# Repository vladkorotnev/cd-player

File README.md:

# ESPer CDP: DIY CD Player with Extra Features

## Index

* [Why a CD Player?](#why-a-cd-player)
* [The structure of an ESPer System](#the-structure-of-an-ESPer-system)
* [Contributing to ESPer](#contributing-to-esper)
* [Using ESPer in your own designs](#using-esper-in-your-own-designs)
* [Where to go further](#where-to-go-further)

## Why a CD Player?

Indeed, it is a very odd project to start in 2025, and continue in 2026. For most people listening to music is a click of a button away in a streaming service, or a local player.

I will not go into the argument of owning vs. borrowing and, frankly, I keep to a more tame stance on the question: it's fine not to own every single piece of media you consume. It's *bad* to *not have an option* to own it, but you also probably don't want to hoard every single that you're only gonna play once and forget about it the day after.

For me the reasons to create ESPer ultimately boil down to:

* **Personal Preference:** I have been collecting CDs for my entire life, with a [very sizeable number](https://www.discogs.com/user/vladkorotnev/collection) to date. My dad has been doing that as well for a good 2/3rds of his life. The CD format is tactile enough to be more interesting than a mouse click, yet convenient enough to be turned into one when the need arises, in contrast to e.g. vinyl. So a CD player to me is as essential as a fridge or a TV, for example. And sure, there are people who don't want one, or don't want a TV, and that's their choice to make.
* **Personal Preference 2:** For a while, microcontrollers in general have not been a very accessible platform. After the Arduino came out some people went as far as to make [CD-players on those](http://singlevalve.web.fc2.com/Atapiduino/atapiduino.htm), but to a newbie me back in the day the circuits looked intimidating. These days manufacturing even custom PCBs is very cheap and options to design them are ample, so it's a chance to take a spin on what I've wanted to do for years.
* **Sustainability:** While CDs are still somewhat active, the *good* players are much less so. You have the usual big brands in massive champagne colored cases which look great and work great, but priced somewhat ridiculous. If you're lucky, you can go to a second-hand store and grab an older model for a more modest price — but who knows if its' days are counted. And you have a lot of the cheaper, bottom of the barrel stuff — i.e. those modern-day players that somehow go out of their way to mess up gapless playback ("tracks" on a CD are akin to a table of contents in a book — it's a list of places where they start and end, alongside a single uninterrupted chunk of audio). Having an open platform based around a commodity item — the computer CD drive — means that as long as one of those is around and working, the player will work, too. Usually when they fail they actually need just a new belt for the tray — and if it's something more fatal then you can always just find a new one.
* **Preservation:** Some old CD drives were *nuts*. Slot loaders? Pioneer made a few, Apple had Matsushita build them for decades. 3.5-inch desktop units? Hey, I can fit [four discs in that](https://youtu.be/9ajyFVKGGHI), says Nakamichi/NEC. Hold my beer, [I'll do SIX!](https://www.instagram.com/p/DFPdWDMTqwi/), responds TEAC. And then those things become basically trash, because no modern computer can really utilize it (and let's be honest, if it can, it probably already has a way more capable drive installed in terms of supported formats). So why not have one sit on your desk and play music instead of decaying in the closet?

## The Structure of an ESPer System

The very first edition (codenamed `ESPER_OG_8M` in the firmware) used a singular, somewhat hastily routed PCB with I2C expanders for the IDE bus. This had its' flaws and strengths, but it's mostly legacy now.

The new ESPer platform going forward consists of four main parts:

1. Processor board: this is where the ESP32 lives along with the buttons and LEDs. Not sure if it's a good idea to combine the buttons onto it but for the compact build it makes more sense.
2. Drive board: this is what plugs into the drive. The flavor depends on the drive you have. The currently planned versions are:
   1. SATA Slimline: you can use this with a laptop SATA drive, because no readymade adapters exist on the market.
   2. IDE/ATAPI/PATA: comes fitted with a plug that can plug right into the drive, a pin header to use a ribbon cable, or both to allow for dual drives in a more compact way than a longer cable. A JAE KX14 50-pin connector can be fitted to use an older laptop IDE drive, or you can connect this to an off-the-shelf IDE-to-SATA translation board to use a desktop-sized SATA drive.
3. IO board: this is what provides power to the whole shebang, and also contains the DAC for the sound to come out of.
   1. Compact variant: made to fit around a laptop drive, has a USB-C 5V input, a DAC, line out 3.5mm jack, headphone jack and a headphone volume wheel.
   2. (Planned) HiFi variant: made with less thoughts given to size for use primarily with desktop drives. Triggers USB-C at 15V or takes a 12V barrel jack, and delivers a separate power line to the bigger desktop drive, while housing a DAC with an RCA line-out, an SPDIF out and a TOSLINK out. Perhaps someday also SPDIF input?
4. Display board: this houses just the display and the infrared receiver alongside it.

The infrared remote is a knockoff Sony RM-D335 with a replaced label to match the functions of the remote in the ESPer menus.

### Accessory Port

The Processor Board is equipped with an "Accessory Port". The use of that is specific to a build, but essentially it's a MOSFET-switched 5V output good for up to an amp.

The logic of it is set by the straps on the main board:

* `000`: the accessory port is active when the player is turned on, and in a non-menu state. This is a good mode to hook up a pass through relay so that another sound source can be chained on the same line for when the player is turned off.
* (planned) `001`: enables the Zoetrope mode. An LED tape installed into a window on the CD drive shall be connected to the output in this mode. When the CD mode is active and a disc is present, the LEDs pulse at a frequency roughly on par with the disc's rotation, chosen experimentally. This allows, at the right lighting conditions, to keep the CD label readable even though it spins very fast. When there is no disc, the LEDs are constantly lit at half the brightness. When a non-CD mode is active, the LEDs turn off.
* Others: reserved.

## Contributing to ESPer

While I do have somewhat strong feelings about that thing being pushed on everyone from all sides for the past few years, I also do acknowledge that in the right hands it does accelerate by a good amount without significant quality reduction. However, to achieve that, we must keep ourselves using the tool to a very high standard.

* **Please test your code.** Not as in unit-tests, but as in flash the firmware and daily drive it for a few. If you have the OG and the Neo revisions, that's awesome! If not, test on which one you have. Get a feel for how it operates, if the UX is any good or there are some annoyances in the operation of the device. If there are, please list them out and we can fix them together. **PRs from users who don't own the hardware will not be accepted in principle.**
* **No machine-generated PR body and docs.** For a non-work project like this, it's not about the hustle, but rather the communication. If you did not take care to see and read through what you want to send in and document it properly, this is insulting to everyone involved, as now the other person must dig through your code themselves to see if the text on the label matches what's actually inside the tin.
* **Machine-generated code must still be readable and understandable for a human.** Not all of us use coding agents. Not all of us can even afford them financially, and not all of us are morally comfortable with how things are right now. Comments should be *sufficient* and formatting should be *sane*. A wall of text for every line is probably not it, though [exceptions do happen](https://github.com/vladkorotnev/plasma-clock/blob/main/src/display/akizuki_k875.cpp#L240-L327) (usually the cursed parts). Something that looks like it was run through a JS minifier is definitely not it.
* **Please don't vibe-code in the bad sense of the term.** While most of the above points already cover it, still do think whether you should do something before seeing whether you can push it into the upstream.

## Using ESPer in your own designs

### Using existing PCBs

You are free to use the PCBs officially provided from this repo as files, or from myself as physical products, to build players for your friends and family. You can even do that for sale, although I would appreciate a donation in such case as well, as this has been an enormous amount of work.

In this case, just make sure you flash the right firmware with the right `FVU_FLAVOR` so that online updates work. It's probably best to install the firmware from the online updater so that it already comes with API tokens and such things used by the official upstream.

### Designing new PCBs

If the hardware matches an official board, and an existing FVU flavor can apply, then the same points as above stand.

Otherwise if you want to change e.g. the pin assignments, please fork this repository and create a new HTTP update source. The existing CI scripts should be good enough. You will then need to point the firmware to update from your server instead.

If your variant gains decent following or you plan to produce it en-masse, feel free to open an issue to add it as an officially supported flavor.

## Where to go further

* [Firmware](firm)
* [Schematics](sch)
* [Test CD files and CUE sheet](test-suite)
* [Hoard of ATAPI-related Docs](reference)

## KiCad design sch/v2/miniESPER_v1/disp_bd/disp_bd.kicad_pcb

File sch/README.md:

# ESPer-CDP Project Schematics Archive

## v1: original ESPer design

Folder: [./v1/]

Format: DipTrace (legacy).

Use with the `OG8M` firmware flavor.

Interfaces:

* ATAPI (slow, command-only)
* I2C expansion ("NIXIEOUT", deprecated/unused)
* 8 button inputs, active low
* RS232 to Futaba GP1232 display (160x32 pixels)
* Line out, 12V out

## v1.5: interface prototype

Folder: [./v1_5]

Partial prototype of a fast ATAPI interface using 2x MCP23S17, 74HC4040AP, 74HC32AP and 74HC123AP in DIP package, as well as AE-LLCNV-LVCH16T245 level shifter breakout board.

Use in conjunction with any ESP32 or the v1 board.

No pre-existing board config exists, create one with the following template:

```c
#define BCONF_IDE_TYPE                          IDEBUS_TYPE_CURSED_SPI
#define BCONF_IDE_SPI_NUM                       VSPI
#define BCONF_IDE_SPI_BURST_PIN                 ...
#define BCONF_IDE_SPI_WRITE_PIN                 ...
#define BCONF_IDE_SPI_CS_PIN                    ...
#define BCONF_IDE_SPI_SCK_PIN                   ...
#define BCONF_IDE_SPI_MISO_PIN                  ...
#define BCONF_IDE_SPI_MOSI_PIN                  ...
#define BCONF_IDE_SPI_RST_PIN                   ...
```

# v2

Work in progress

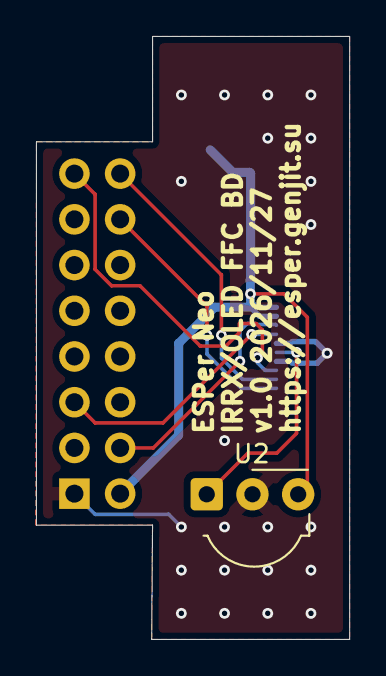
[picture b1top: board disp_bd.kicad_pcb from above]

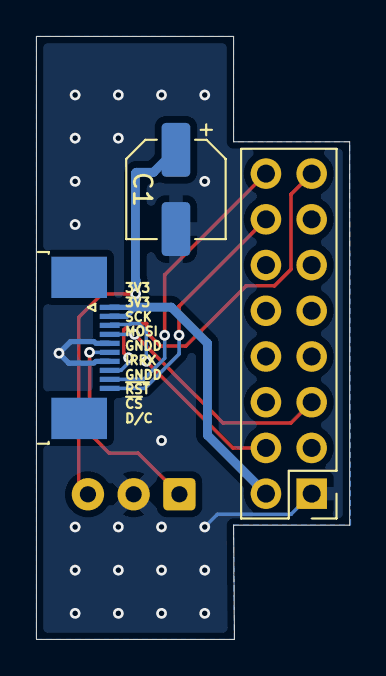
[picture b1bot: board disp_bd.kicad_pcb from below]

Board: 2 copper layers, 17.4 x 33.5 mm, 4 parts (3 on the bottom side), 8 nets.

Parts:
C1: C_Polarized; CP_Elec_5x3
J2: To_Main_Bd; TE_1-1734839-0_1x10-1MP_P0.5mm_Horizontal
OLED1: PinHeader_2x08_P2.54mm_Vertical
U2: TSOP43xx; Vishay_MOLD-3Pin

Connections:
+3V3: C1.1, J2.1, J2.2, OLED1.2 (VCC), U2.3 (Vs)
DISP_CS: J2.9, OLED1.16 (~CS)
DISP_DC: J2.10, OLED1.14 (D/~C)
DISP_MOSI: J2.4, OLED1.5 (MOSI/D1)
DISP_SCK: J2.3, OLED1.4 (SCK/D0)
GNDD: C1.2, J2.5, J2.7, OLED1.1 (GND), U2.2 (GND)
IR_RX: J2.6, U2.1 (OUT)
~RESET: J2.8, OLED1.15 (~RES)

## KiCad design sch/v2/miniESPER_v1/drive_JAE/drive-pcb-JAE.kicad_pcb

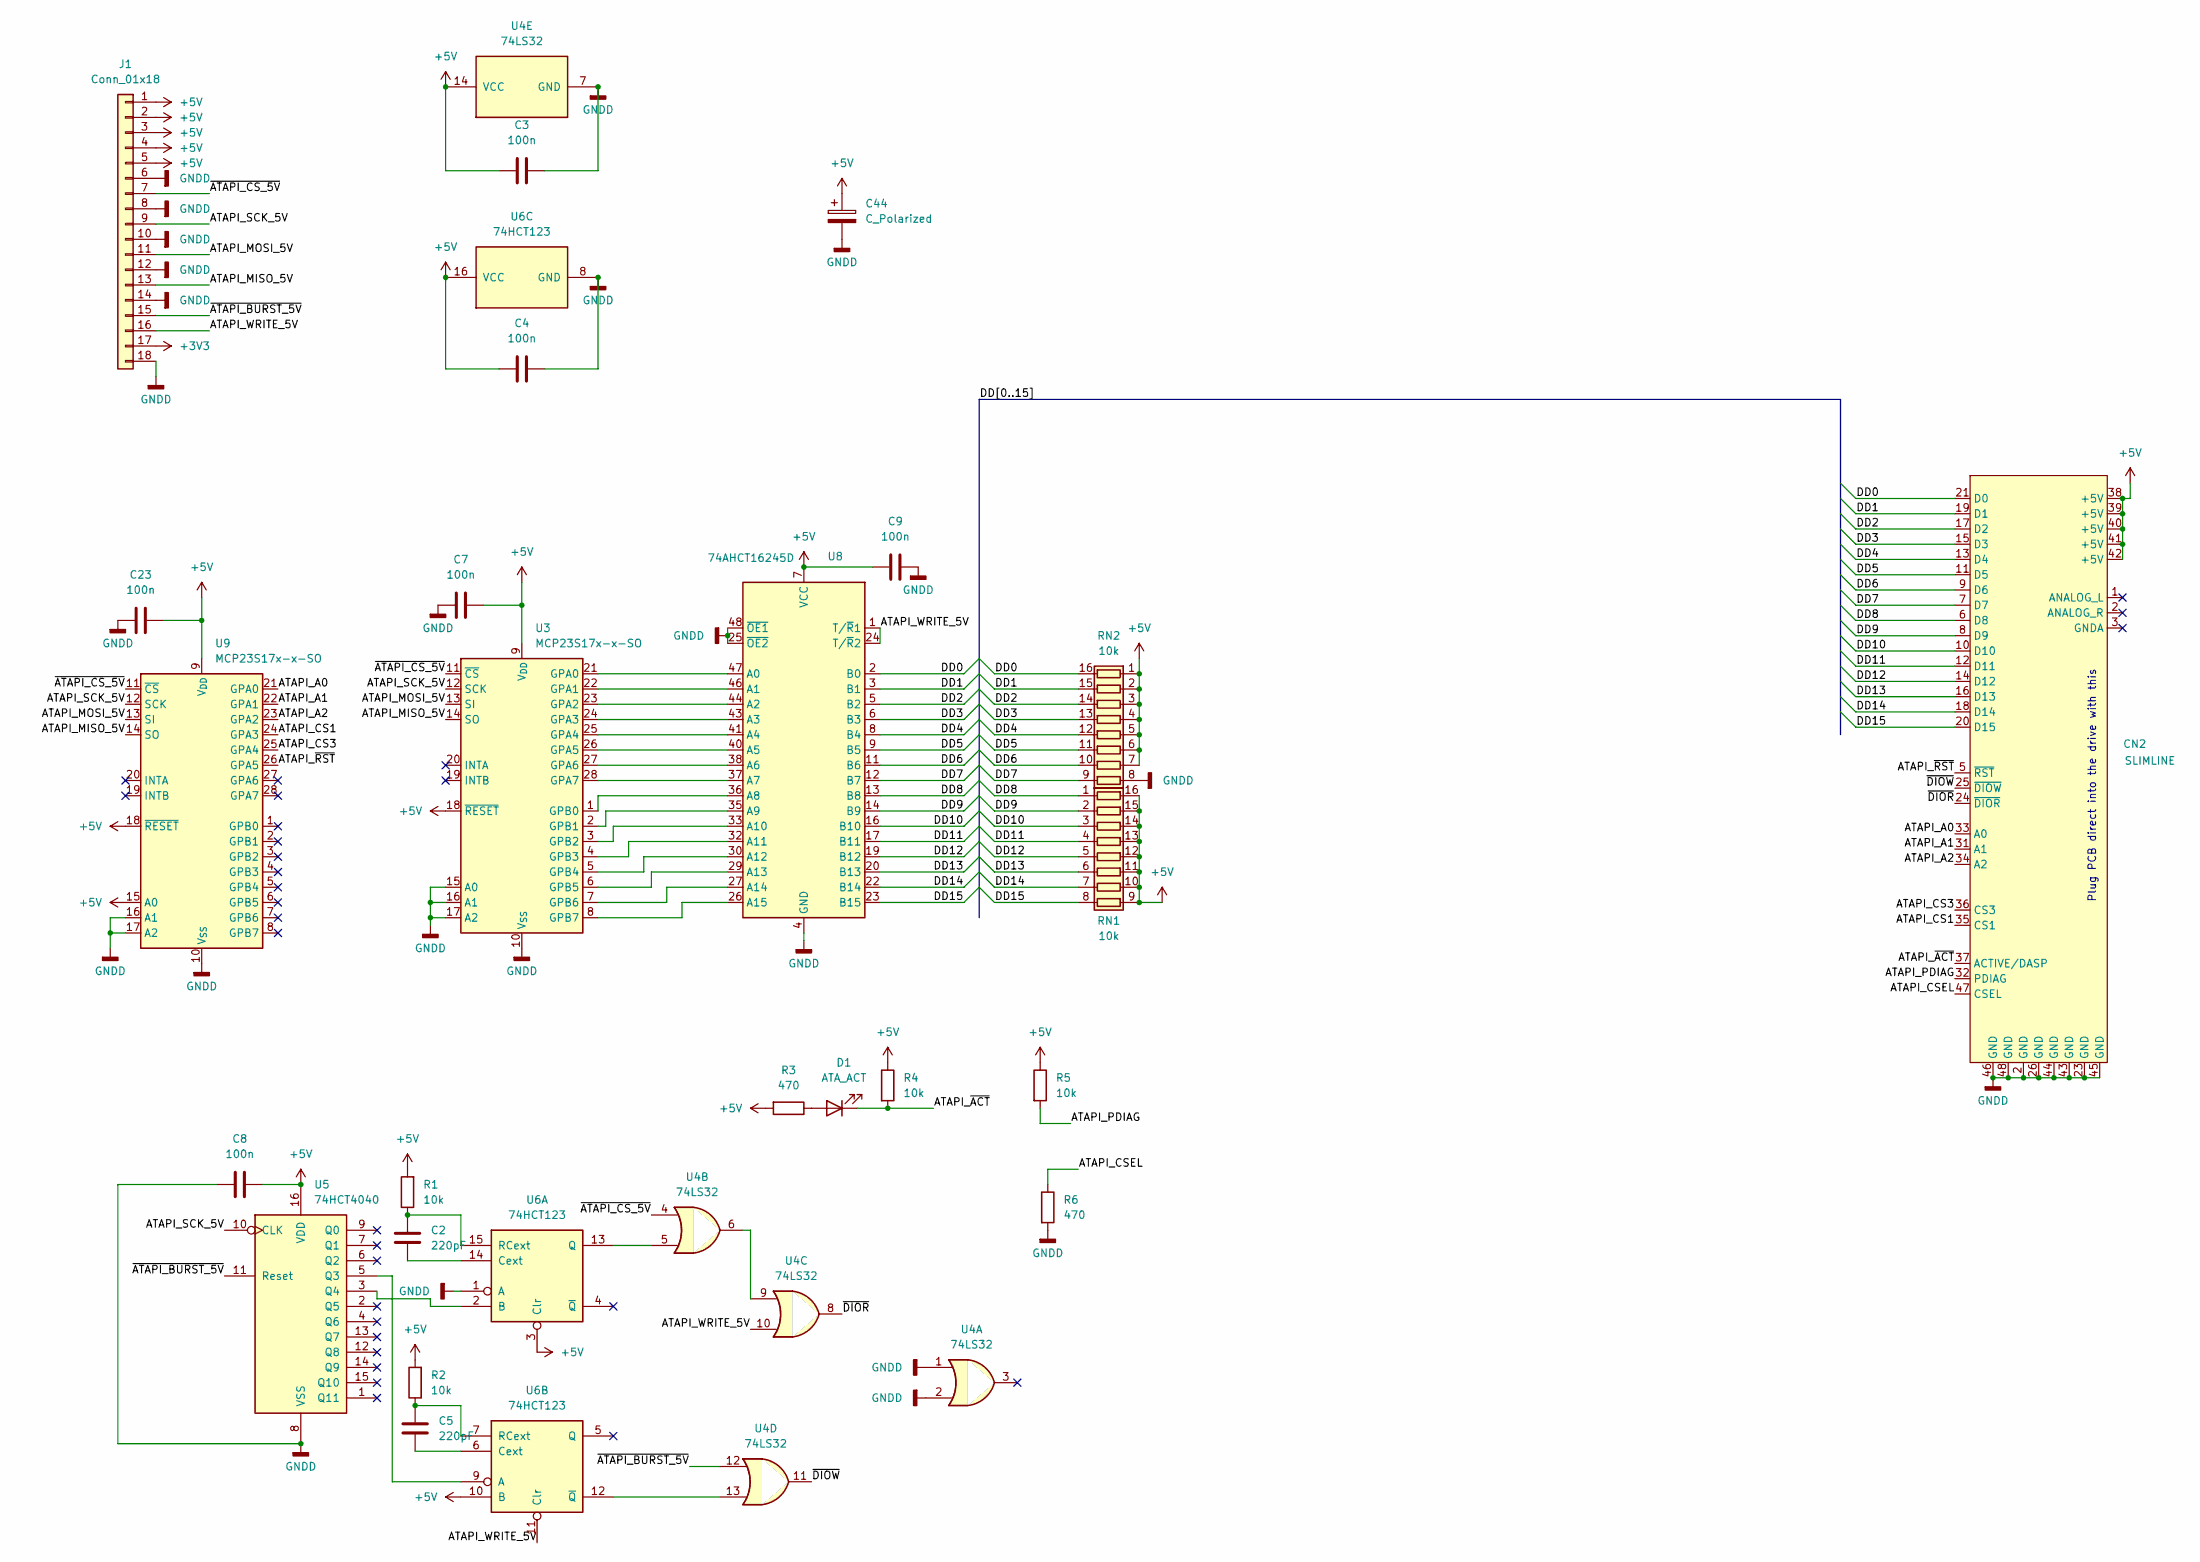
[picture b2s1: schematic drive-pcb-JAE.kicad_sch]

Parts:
C2, C5: 220pF; C_1206_3216Metric
C3, C4, C7, C8, C9, C23: 100n; C_1206_3216Metric
C44: C_Polarized; CP_Elec_5x4.5
CN2: SLIMLINE; JAE_KX14-50K2DE
D1: ATA_ACT; LED_1206_3216Metric_Pad1.42x1.75mm_HandSolder
J1: Conn_01x18; TE_1-1734839-8_1x18-1MP_P0.5mm_Horizontal
R1, R2, R4, R5: 10k; R_1206_3216Metric_Pad1.30x1.75mm_HandSolder
R3, R6: 470; R_1206_3216Metric_Pad1.30x1.75mm_HandSolder
RN1, RN2: 10k; R_Array_Convex_8x0602
U3, U9: MCP23S17x-x-SO; SSOP-28_5.3x10.2mm_P0.65mm
U4: 74LS32; SO-14_3.9x8.65mm_P1.27mm
U5: 74HCT4040; SO-16_3.9x9.9mm_P1.27mm
U6: 74HCT123; SO-16_3.9x9.9mm_P1.27mm
U8: 74AHCT16245D; TSSOP-48_6.1x12.5mm_P0.5mm

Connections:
+3V3: J1.17
+5V: C3.1, C4.1, C7.2, C8.2, C9.1, C23.2, C44.1, CN2.38 (+5V), CN2.39 (+5V), CN2.40 (+5V), CN2.41 (+5V), CN2.42 (+5V), J1.1, J1.2, J1.3, J1.4, J1.5, R1.2, R2.2, R3.2, R4.1, R5.1, RN1.9 (R8.2), RN1.10 (R7.2), RN1.11 (R6.2), RN1.12 (R5.2), RN1.13 (R4.2), RN1.14 (R3.2), RN1.15 (R2.2), RN1.16 (R1.2), RN2.1 (R1.1), RN2.2 (R2.1), RN2.3 (R3.1), RN2.4 (R4.1), RN2.5 (R5.1), RN2.6 (R6.1), RN2.7 (R7.1), U3.9 (V_{DD}), U3.18 (~RESET), U4.14 (VCC), U5.16 (VDD), U6.3 (Clr), U6.10 (B), U6.16 (VCC), U8.7 (VCC), U8.18 (VCC), U8.31 (VCC), U8.42 (VCC), U9.9 (V_{DD}), U9.15 (A0), U9.18 (~RESET)
/ATAPI_A0: CN2.33 (A0), U9.21 (GPA0)
/ATAPI_A1: CN2.31 (A1), U9.22 (GPA1)
/ATAPI_A2: CN2.34 (A2), U9.23 (GPA2)
/ATAPI_CS1: CN2.35 (CS1), U9.24 (GPA3)
/ATAPI_CS3: CN2.36 (CS3), U9.25 (GPA4)
/ATAPI_CSEL: CN2.47 (CSEL), R6.1
/ATAPI_MISO_5V: J1.13, U3.14 (SO), U9.14 (SO)
/ATAPI_MOSI_5V: J1.11, U3.13 (SI), U9.13 (SI)
/ATAPI_PDIAG: CN2.32 (PDIAG), R5.2
/ATAPI_SCK_5V: J1.9, U3.12 (SCK), U5.10 (CLK), U9.12 (SCK)
/ATAPI_WRITE_5V: J1.16, U4.10, U6.11 (Clr), U8.1 (T/~R1), U8.24 (T/~R2)
/ATAPI_~ACT: CN2.37 (ACTIVE/DASP), D1.1 (K), R4.2; also elsewhere on the board
/ATAPI_~RST: CN2.5 (~RST), U9.26 (GPA5)
/DD0: CN2.21 (D0), RN2.16 (R1.2), U8.2 (B0)
/DD1: CN2.19 (D1), RN2.15 (R2.2), U8.3 (B1)
/DD2: CN2.17 (D2), RN2.14 (R3.2), U8.5 (B2)
/DD3: CN2.15 (D3), RN2.13 (R4.2), U8.6 (B3)
/DD4: CN2.13 (D4), RN2.12 (R5.2), U8.8 (B4)
/DD5: CN2.11 (D5), RN2.11 (R6.2), U8.9 (B5)
/DD6: CN2.9 (D6), RN2.10 (R7.2), U8.11 (B6)
/DD7: CN2.7 (D7), RN2.9 (R8.2), U8.12 (B7)
/DD8: CN2.6 (D8), RN1.1 (R1.1), U8.13 (B8)
/DD9: CN2.8 (D9), RN1.2 (R2.1), U8.14 (B9)
/DD10: CN2.10 (D10), RN1.3 (R3.1), U8.16 (B10)
/DD11: CN2.12 (D11), RN1.4 (R4.1), U8.17 (B11)
/DD12: CN2.14 (D12), RN1.5 (R5.1), U8.19 (B12)
/DD13: CN2.16 (D13), RN1.6 (R6.1), U8.20 (B13)
/DD14: CN2.18 (D14), RN1.7 (R7.1), U8.22 (B14)
/DD15: CN2.20 (D15), RN1.8 (R8.1), U8.23 (B15)
/~ATAPI_BURST_5V: J1.15, U4.12, U5.11 (Reset)
/~ATAPI_CS_5V: J1.7, U3.11 (~CS), U4.4, U9.11 (~CS)
/~DIOR: CN2.24 (~DIOR), U4.8
/~DIOW: CN2.25 (~DIOW), U4.11
GNDD: C3.2, C4.2, C7.1, C8.1, C9.2, C23.1, C44.2, CN2.2 (GND), CN2.23 (GND), CN2.26 (GND), CN2.43 (GND), CN2.44 (GND), CN2.45 (GND), CN2.46 (GND), CN2.48 (GND), J1.6, J1.8, J1.10, J1.12, J1.14, J1.18, R6.2, RN2.8 (R8.1), U3.10 (V_{SS}), U3.15 (A0), U3.16 (A1), U3.17 (A2), U4.1, U4.2, U4.7 (GND), U5.8 (VSS), U6.1 (A), U6.8 (GND), U8.4 (GND), U8.10 (GND), U8.15 (GND), U8.21 (GND), U8.25 (~OE2), U8.28 (GND), U8.34 (GND), U8.39 (GND), U8.45 (GND), U8.48 (~OE1), U9.10 (V_{SS}), U9.16 (A1), U9.17 (A2)
unnamed 36: D1.2 (A), R3.1; also elsewhere on the board
unnamed: U3.21 (GPA0), U8.47 (A0)
unnamed: U3.22 (GPA1), U8.46 (A1)
unnamed: U3.23 (GPA2), U8.44 (A2)
unnamed: U3.24 (GPA3), U8.43 (A3)
unnamed: U3.25 (GPA4), U8.41 (A4)
unnamed: U3.26 (GPA5), U8.40 (A5)
unnamed: U3.27 (GPA6), U8.38 (A6)
unnamed: U3.28 (GPA7), U8.37 (A7)
unnamed: U3.1 (GPB0), U8.36 (A8)
unnamed: U3.2 (GPB1), U8.35 (A9)
unnamed: U3.3 (GPB2), U8.33 (A10)
unnamed: U3.4 (GPB3), U8.32 (A11)
unnamed: U3.5 (GPB4), U8.30 (A12)
unnamed: U3.6 (GPB5), U8.29 (A13)
unnamed: U3.7 (GPB6), U8.27 (A14)
unnamed: U3.8 (GPB7), U8.26 (A15)
unnamed: U4.6, U4.9
unnamed: U5.5 (Q3), U6.9 (A)
unnamed: U5.3 (Q4), U6.2 (B)
unnamed: C2.1, U6.14 (Cext)
unnamed: U4.5, U6.13 (Q)
unnamed: C2.2, R1.1, U6.15 (RCext)
unnamed: C5.1, U6.6 (Cext)
unnamed: C5.2, R2.1, U6.7 (RCext)
unnamed: U4.13, U6.12 (~Q)

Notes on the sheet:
Plug PCB direct into the drive with this

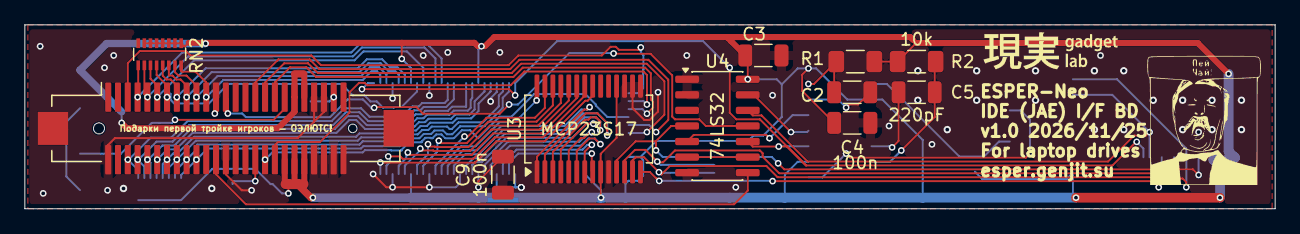
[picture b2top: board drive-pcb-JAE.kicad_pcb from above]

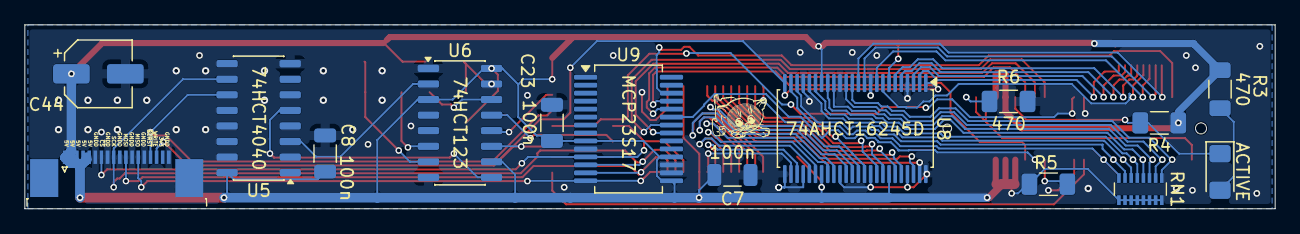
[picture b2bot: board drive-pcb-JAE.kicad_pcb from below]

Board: 2 copper layers, 102.0 x 15.0 mm, 26 parts (15 on the bottom side), 61 nets.

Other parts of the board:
ACTIVE: ATA_ACT; LED_1206_3216Metric_Pad1.42x1.75mm_HandSolder

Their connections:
/ATAPI_~ACT: ACTIVE.1 (K); also elsewhere on the board
unnamed 36: ACTIVE.2 (A); also elsewhere on the board

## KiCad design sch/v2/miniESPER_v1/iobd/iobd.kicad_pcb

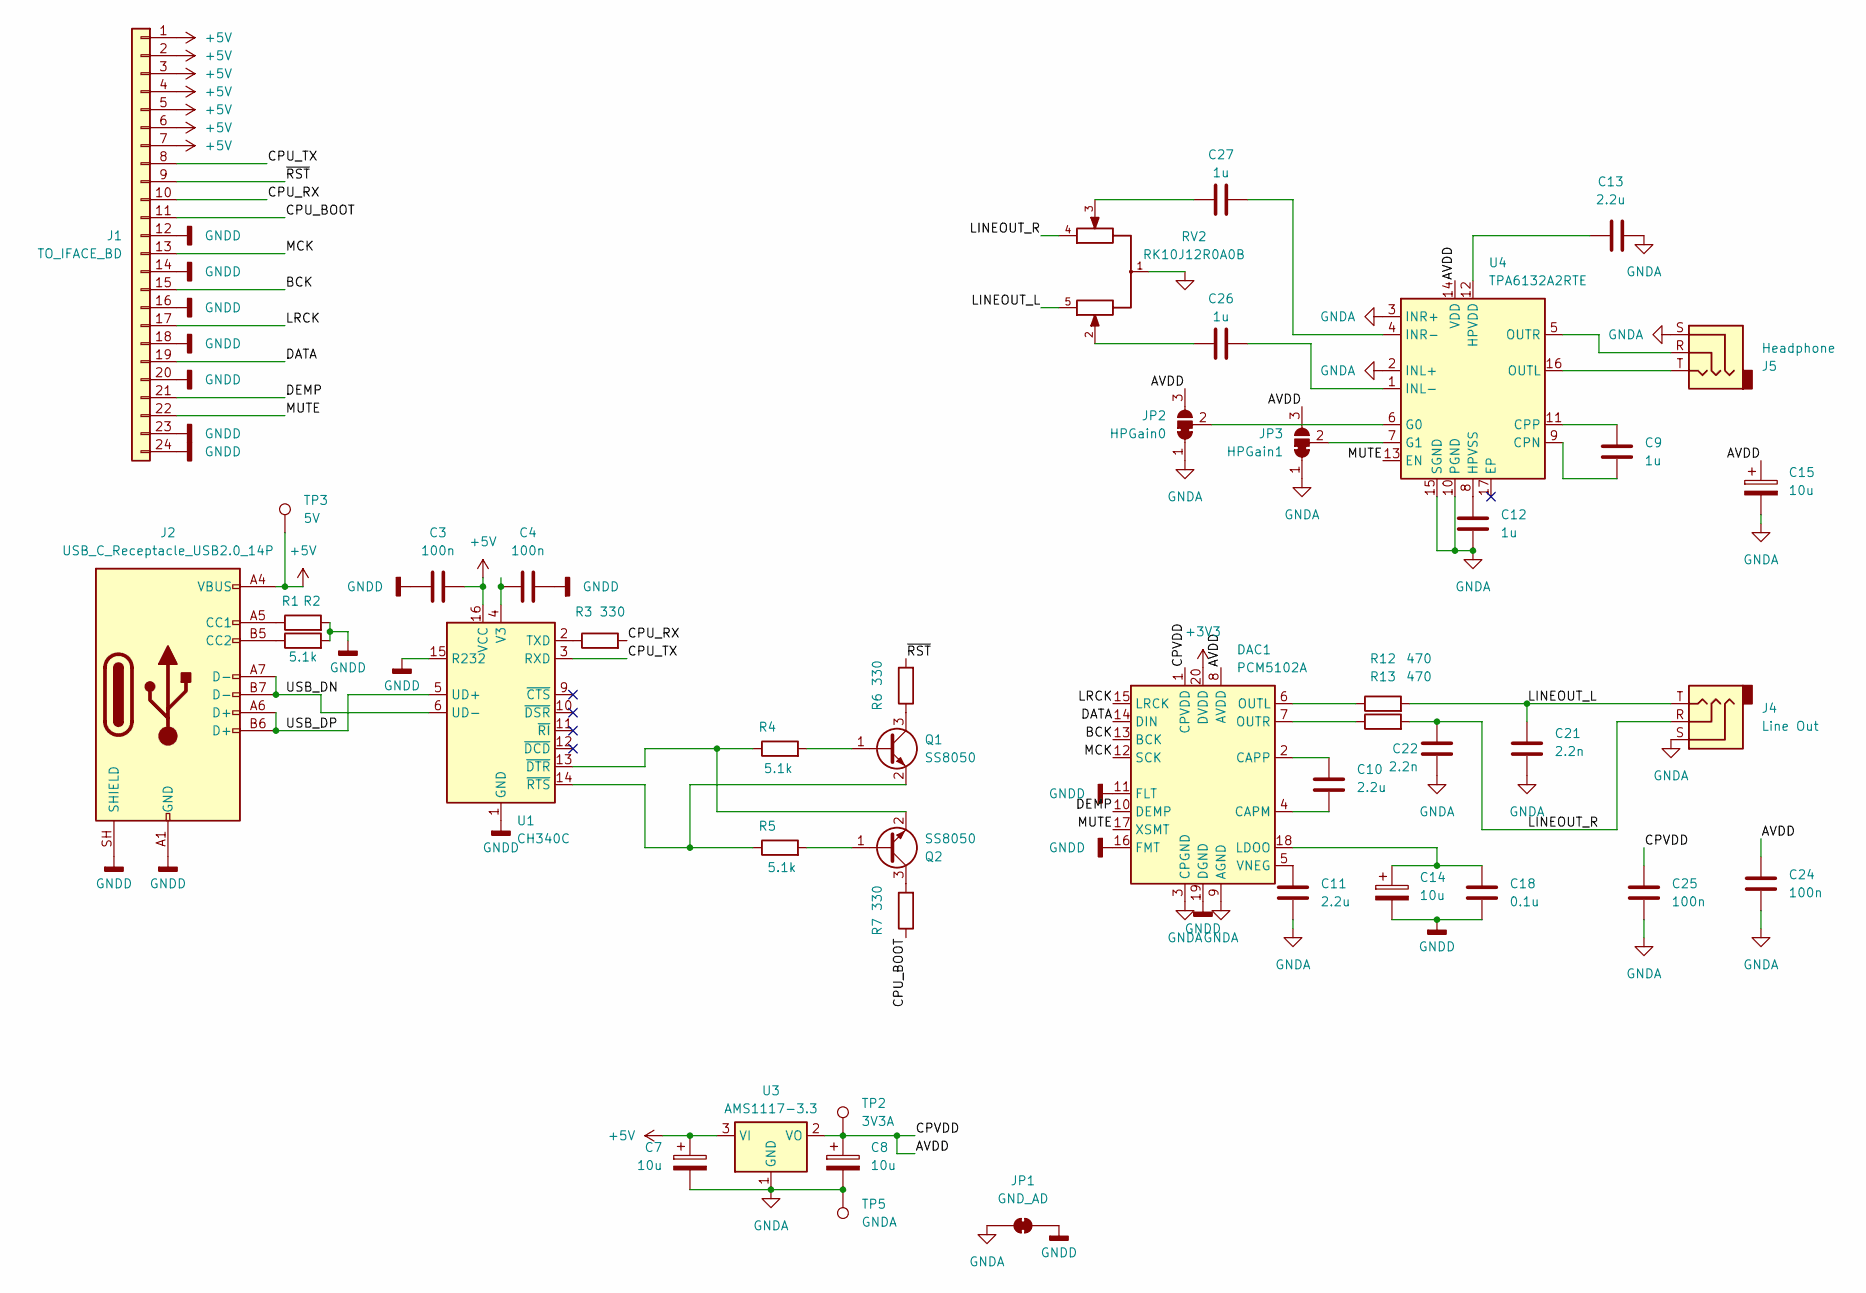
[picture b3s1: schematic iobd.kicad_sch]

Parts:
C3, C4: 100n; C_1206_3216Metric_Pad1.33x1.80mm_HandSolder
C7, C8, C14, C15: 10u; CP_Elec_4x5.4
C9, C12: 1u; C_1206_3216Metric_Pad1.33x1.80mm_HandSolder
C10: 2.2u; C_0805_2012Metric
C11: 2.2u; C_1206_3216Metric_Pad1.33x1.80mm_HandSolder
C13: 2.2u; C_0603_1608Metric
C18: 0.1u; C_1206_3216Metric_Pad1.33x1.80mm_HandSolder
C21, C22: 2.2n; C_0603_1608Metric
C24, C25: 100n; C_0603_1608Metric
C26, C27: 1u; C_0603_1608Metric
DAC1: PCM5102A; TSSOP-20_4.4x6.5mm_P0.65mm
J1: TO_IFACE_BD; TE_2-1734839-4_1x24-1MP_P0.5mm_Horizontal
J2: USB_C_Receptacle_USB2.0_14P; USB_C_Receptacle_HRO_TYPE-C-31-M-12
J4: Line Out; Jack_3.5mm_CUI_SJ-3524-SMT_Horizontal
J5: Headphone; Jack_3.5mm_CUI_SJ-3524-SMT_Horizontal
JP1: GND_AD; SolderJumper-2_P1.3mm_Bridged_RoundedPad1.0x1.5mm
JP2: HPGain0; SolderJumper-3_P1.3mm_Bridged12_RoundedPad1.0x1.5mm
JP3: HPGain1; SolderJumper-3_P1.3mm_Bridged12_RoundedPad1.0x1.5mm
Q1, Q2: SS8050; SOT-23
R1, R2, R4, R5: 5.1k; R_1206_3216Metric_Pad1.30x1.75mm_HandSolder
R3, R6, R7: 330; R_1206_3216Metric_Pad1.30x1.75mm_HandSolder
R12, R13: 470; R_0603_1608Metric
RV2: RK10J12R0A0B
TP2: 3V3A; TestPoint_Pad_D1.5mm
TP3: 5V; TestPoint_Pad_D1.5mm
TP5: GNDA; TestPoint_Pad_D1.5mm
U1: CH340C; SOIC-16_3.9x9.9mm_P1.27mm
U3: AMS1117-3.3; SOT-223-3_TabPin2
U4: TPA6132A2RTE; WQFN-16-1EP_3x3mm_P0.5mm_EP1.6x1.6mm

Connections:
+3V3: DAC1.20 (DVDD)
+5V: C3.2, C7.1, J1.1, J1.2, J1.3, J1.4, J1.5, J1.6, J1.7, J2.A4 (VBUS), J2.A9 (VBUS), J2.B4 (VBUS), J2.B9 (VBUS), TP3.1 (1_1), U1.16 (VCC), U3.3 (VI)
/AVDD: C8.1, C15.1, C24.2, C25.2, DAC1.1 (CPVDD), DAC1.8 (AVDD), JP2.3 (B), JP3.3 (B), TP2.1, U3.2 (VO), U4.14 (VDD)
/BCK: DAC1.13 (BCK), J1.15
/CPU_BOOT: J1.11, R7.1
/CPU_RX: J1.10, R3.2
/CPU_TX: J1.8, U1.3 (RXD)
/DATA: DAC1.14 (DIN), J1.19
/DEMP: DAC1.10 (DEMP), J1.21
/LINEOUT_L: C21.1, J4.T, R12.2, RV2.5 (R1_END_3)
/LINEOUT_R: C22.1, J4.R, R13.2, RV2.4 (R2_END_3)
/LRCK: DAC1.15 (LRCK), J1.17
/MCK: DAC1.12 (SCK), J1.13
/MUTE: DAC1.17 (XSMT), J1.22, U4.13 (EN)
/USB_DN: J2.A7 (D-), J2.B7 (D-), U1.6 (UD-)
/USB_DP: J2.A6 (D+), J2.B6 (D+), U1.5 (UD+)
/~RST: J1.9, R6.2
GNDA: C7.2, C8.2, C11.2, C12.2, C13.2, C15.2, C21.2, C22.2, C24.1, C25.1, DAC1.3 (CPGND), DAC1.9 (AGND), J4.S, J5.S, JP1.1 (A), JP2.1 (A), JP3.1 (A), RV2.1 (COMMON_1), TP5.1, U3.1 (GND), U4.2 (INL+), U4.3 (INR+), U4.10 (PGND), U4.15 (SGND)
GNDD: C3.1, C4.2, C14.2, C18.2, DAC1.11 (FLT), DAC1.16 (FMT), DAC1.19 (DGND), J1.12, J1.14, J1.16, J1.18, J1.20, J1.23, J1.24, J2.A1 (GND), J2.A12 (GND), J2.B1 (GND), J2.B12 (GND), J2.SH (SHIELD), JP1.2 (B), R1.2, R2.2, U1.1 (GND), U1.15 (R232)
unnamed: C10.2, DAC1.4 (CAPM)
unnamed: C10.1, DAC1.2 (CAPP)
unnamed: C14.1, C18.1, DAC1.18 (LDOO)
unnamed: DAC1.6 (OUTL), R12.1
unnamed: DAC1.7 (OUTR), R13.1
unnamed: C11.1, DAC1.5 (VNEG)
unnamed: J2.A5 (CC1), R1.1
unnamed: J2.B5 (CC2), R2.1
unnamed: JP2.2 (C), U4.6 (G0)
unnamed: JP3.2 (C), U4.7 (G1)
unnamed: Q1.1 (B), R4.2
unnamed: Q1.3 (C), R6.1
unnamed: Q1.2 (E), R5.1, U1.14 (~RTS)
unnamed: Q2.1 (B), R5.2
unnamed: Q2.3 (C), R7.2
unnamed: Q2.2 (E), R4.1, U1.13 (~DTR)
unnamed: C26.1, RV2.2 (R1_WIPER)
unnamed: C27.1, RV2.3 (R2_WIPER)
unnamed: R3.1, U1.2 (TXD)
unnamed: C4.1, U1.4 (V3)
unnamed: C9.2, U4.9 (CPN)
unnamed: C9.1, U4.11 (CPP)
unnamed: C13.1, U4.12 (HPVDD)
unnamed: C12.1, U4.8 (HPVSS)
unnamed: C26.2, U4.1 (INL-)
unnamed: C27.2, U4.4 (INR-)
unnamed: J5.T, U4.16 (OUTL)
unnamed: J5.R, U4.5 (OUTR)

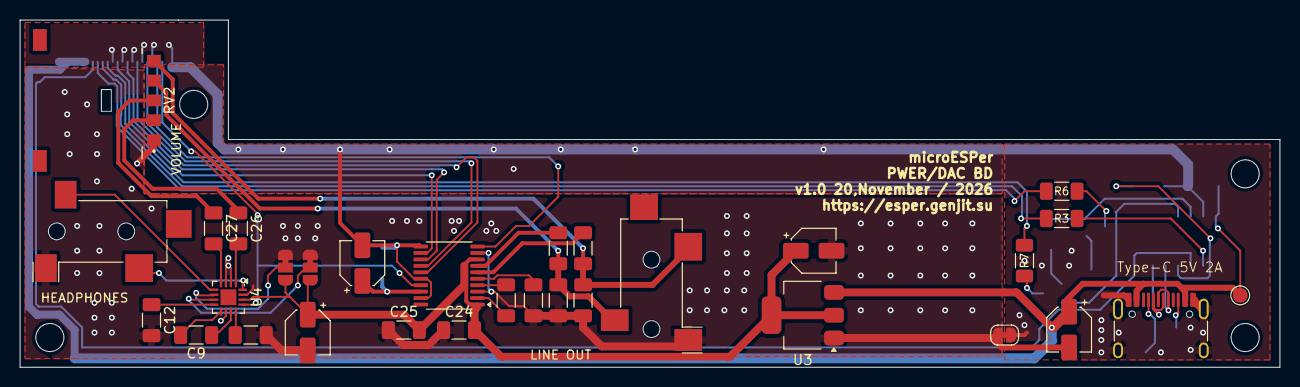
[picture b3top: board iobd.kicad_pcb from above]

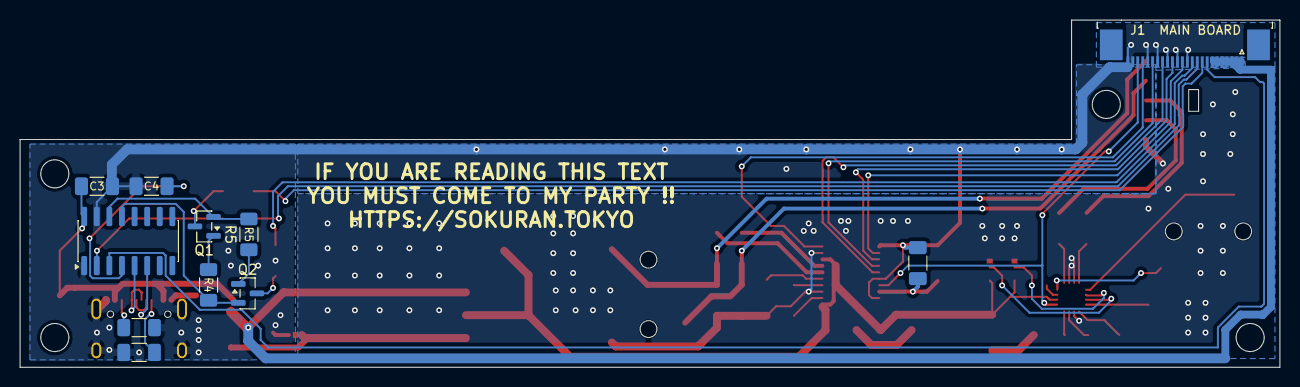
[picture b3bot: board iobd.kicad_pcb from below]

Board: 2 copper layers, 127.0 x 35.0 mm, 42 parts (11 on the bottom side), 46 nets.

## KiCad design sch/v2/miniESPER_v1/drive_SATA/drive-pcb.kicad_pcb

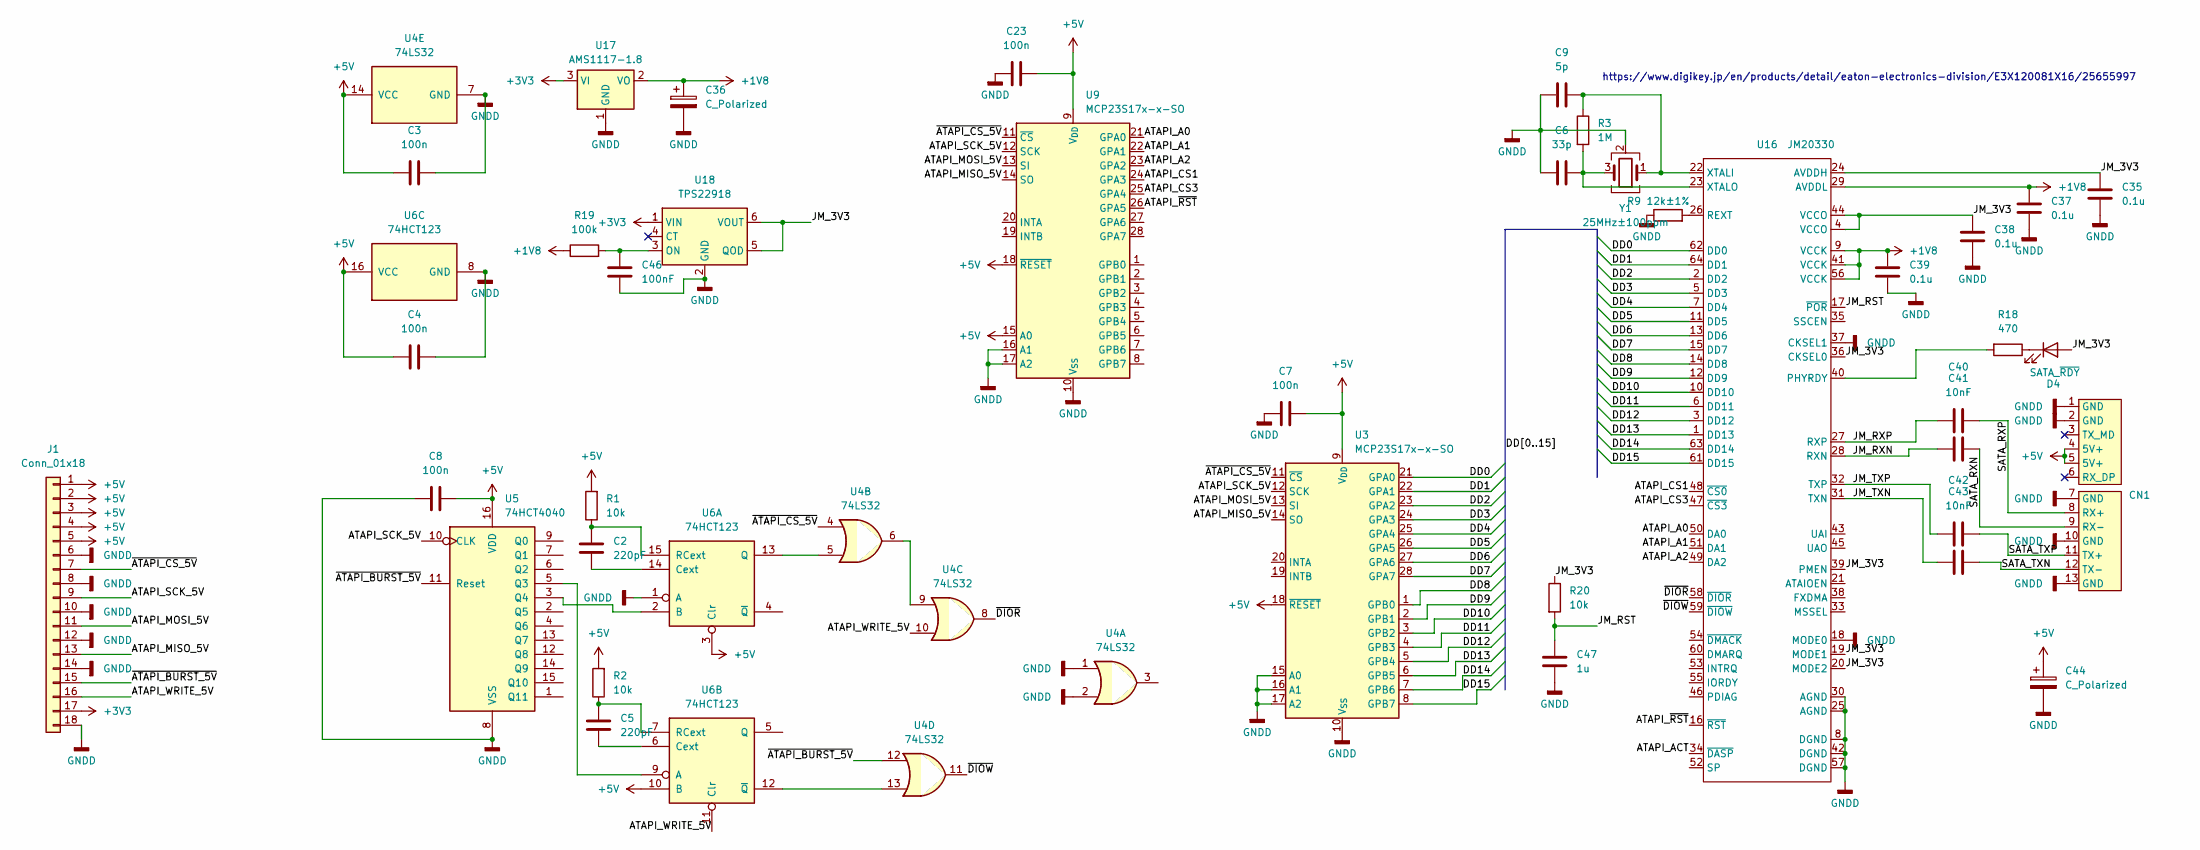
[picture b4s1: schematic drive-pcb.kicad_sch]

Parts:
C2, C5: 220pF; C_1206_3216Metric
C3, C4, C7, C8, C23: 100n; C_1206_3216Metric
C6: 33p; C_1206_3216Metric_Pad1.33x1.80mm_HandSolder
C9: 5p; C_1206_3216Metric_Pad1.33x1.80mm_HandSolder
C35, C37, C38, C39: 0.1u; C_1206_3216Metric_Pad1.33x1.80mm_HandSolder
C36, C44: C_Polarized; CP_Elec_5x4.5
C40, C41, C42, C43: 10nF; C_1206_3216Metric_Pad1.33x1.80mm_HandSolder
C46: 100nF; C_1206_3216Metric_Pad1.33x1.80mm_HandSolder
C47: 1u; C_1206_3216Metric_Pad1.33x1.80mm_HandSolder
CN1: TE CONN 1735539-2
D4: SATA_~{RDY}; LED_1206_3216Metric_Pad1.42x1.75mm_HandSolder
J1: Conn_01x18; TE_1-1734839-8_1x18-1MP_P0.5mm_Horizontal
R1, R2, R20: 10k; R_1206_3216Metric_Pad1.30x1.75mm_HandSolder
R3: 1M; R_1206_3216Metric_Pad1.30x1.75mm_HandSolder
R9: 12k±1%; R_1206_3216Metric_Pad1.30x1.75mm_HandSolder
R18: 470; R_1206_3216Metric_Pad1.30x1.75mm_HandSolder
R19: 100k; R_1206_3216Metric_Pad1.30x1.75mm_HandSolder
U3, U9: MCP23S17x-x-SO; SSOP-28_5.3x10.2mm_P0.65mm
U4: 74LS32
U5: 74HCT4040; SO-16_3.9x9.9mm_P1.27mm
U6: 74HCT123
U16: JM20330; TQFP-64_10x10mm_P0.5mm
U17: AMS1117-1.8; SOT-223-3_TabPin2
U18: TPS22918; SOT-23-6
Y1: 25MHz±100ppm; Crystal_SMD_3225-4Pin_3.2x2.5mm_HandSoldering

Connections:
+1V8: C36.1, C37.1, C39.1, R19.1, U16.9 (VCCK), U16.29 (AVDDL), U16.41 (VCCK), U16.56 (VCCK), U17.2 (VO)
+3V3: J1.17, U17.3 (VI), U18.1 (VIN)
+5V: C3.1, C4.1, C7.2, C8.2, C23.2, C44.1, CN1.4 (5V+), CN1.5 (5V+), J1.1, J1.2, J1.3, J1.4, J1.5, R1.2, R2.2, U3.9 (V_{DD}), U3.18 (~RESET), U4.14 (VCC), U5.16 (VDD), U6.3 (Clr), U6.10 (B), U6.16 (VCC), U9.9 (V_{DD}), U9.15 (A0), U9.18 (~RESET)
/ATAPI_A0: U9.21 (GPA0), U16.50 (DA0)
/ATAPI_A1: U9.22 (GPA1), U16.51 (DA1)
/ATAPI_A2: U9.23 (GPA2), U16.49 (DA2)
/ATAPI_ACT: U16.34 (~DASP)
/ATAPI_CS1: U9.24 (GPA3), U16.48 (~CS0)
/ATAPI_CS3: U9.25 (GPA4), U16.47 (~CS3)
/ATAPI_MISO_5V: J1.13, U3.14 (SO), U9.14 (SO)
/ATAPI_MOSI_5V: J1.11, U3.13 (SI), U9.13 (SI)
/ATAPI_SCK_5V: J1.9, U3.12 (SCK), U5.10 (CLK), U9.12 (SCK)
/ATAPI_WRITE_5V: J1.16, U4.10, U6.11 (Clr)
/ATAPI_~RST: U9.26 (GPA5), U16.16 (~RST)
/DD0: U3.21 (GPA0), U16.62 (DD0)
/DD1: U3.22 (GPA1), U16.64 (DD1)
/DD2: U3.23 (GPA2), U16.2 (DD2)
/DD3: U3.24 (GPA3), U16.5 (DD3)
/DD4: U3.25 (GPA4), U16.7 (DD4)
/DD5: U3.26 (GPA5), U16.11 (DD5)
/DD6: U3.27 (GPA6), U16.13 (DD6)
/DD7: U3.28 (GPA7), U16.15 (DD7)
/DD8: U3.1 (GPB0), U16.14 (DD8)
/DD9: U3.2 (GPB1), U16.12 (DD9)
/DD10: U3.3 (GPB2), U16.10 (DD10)
/DD11: U3.4 (GPB3), U16.6 (DD11)
/DD12: U3.5 (GPB4), U16.3 (DD12)
/DD13: U3.6 (GPB5), U16.1 (DD13)
/DD14: U3.7 (GPB6), U16.63 (DD14)
/DD15: U3.8 (GPB7), U16.61 (DD15)
/JM_3V3: C35.1, C38.1, D4.2 (A), R20.1, U16.4 (VCCO), U16.19 (MODE1), U16.20 (MODE2), U16.24 (AVDDH), U16.36 (CKSEL0), U16.39 (PMEN), U16.44 (VCCO), U18.5 (QOD), U18.6 (VOUT)
/JM_RST: C47.1, R20.2, U16.17 (~POR)
/JM_RXN: C41.1, U16.28 (RXN)
/JM_RXP: C40.1, U16.27 (RXP)
/JM_TXN: C43.1, U16.31 (TXN)
/JM_TXP: C42.1, U16.32 (TXP)
/SATA_RXN: C41.2, CN1.9 (RX-)
/SATA_RXP: C40.2, CN1.8 (RX+)
/SATA_TXN: C43.2, CN1.12 (TX-)
/SATA_TXP: C42.2, CN1.11 (TX+)
/~ATAPI_BURST_5V: J1.15, U4.12, U5.11 (Reset)
/~ATAPI_CS_5V: J1.7, U3.11 (~CS), U4.4, U9.11 (~CS)
/~DIOR: U4.8, U16.58 (~DIOR)
/~DIOW: U4.11, U16.59 (~DIOW)
GNDD: C3.2, C4.2, C6.1, C7.1, C8.1, C9.1, C23.1, C35.2, C36.2, C37.2, C38.2, C39.2, C44.2, C46.2, C47.2, CN1.1 (GND), CN1.2 (GND), CN1.7 (GND), CN1.10 (GND), CN1.13 (GND), J1.6, J1.8, J1.10, J1.12, J1.14, J1.18, R9.1, U3.10 (V_{SS}), U3.15 (A0), U3.16 (A1), U3.17 (A2), U4.1, U4.2, U4.7 (GND), U5.8 (VSS), U6.1 (A), U6.8 (GND), U9.10 (V_{SS}), U9.16 (A1), U9.17 (A2), U16.8 (DGND), U16.18 (MODE0), U16.25 (AGND), U16.30 (AGND), U16.37 (CKSEL1), U16.42 (DGND), U16.57 (DGND), U17.1 (GND), U18.2 (GND), Y1.2 (G), Y1.4 (G)
unnamed: D4.1 (K), R18.1
unnamed: U4.6, U4.9
unnamed: U5.5 (Q3), U6.9 (A)
unnamed: U5.3 (Q4), U6.2 (B)
unnamed: C2.1, U6.14 (Cext)
unnamed: U4.5, U6.13 (Q)
unnamed: C2.2, R1.1, U6.15 (RCext)
unnamed: C5.1, U6.6 (Cext)
unnamed: C5.2, R2.1, U6.7 (RCext)
unnamed: U4.13, U6.12 (~Q)
unnamed: R18.2, U16.40 (PHYRDY)
unnamed: R9.2, U16.26 (REXT)
unnamed: C9.2, R3.1, U16.22 (XTALI), Y1.1
unnamed: C6.2, R3.2, U16.23 (XTALO), Y1.3
unnamed: C46.1, R19.2, U18.3 (ON)

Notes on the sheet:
https://www.digikey.jp/en/products/detail/eaton-electronics-division/E3X120081X16/25655997

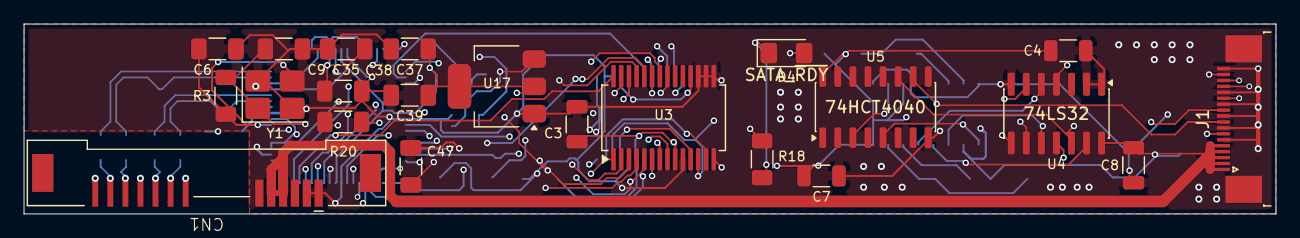
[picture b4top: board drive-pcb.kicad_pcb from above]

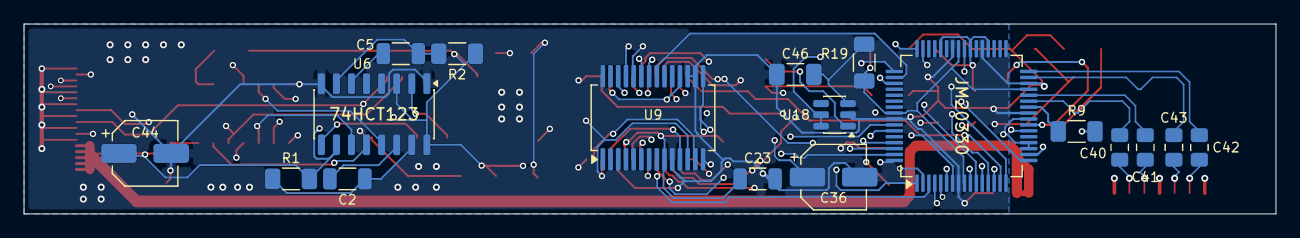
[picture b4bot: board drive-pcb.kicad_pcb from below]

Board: 4 copper layers, 105.5 x 16.0 mm, 40 parts (18 on the bottom side), 59 nets.
